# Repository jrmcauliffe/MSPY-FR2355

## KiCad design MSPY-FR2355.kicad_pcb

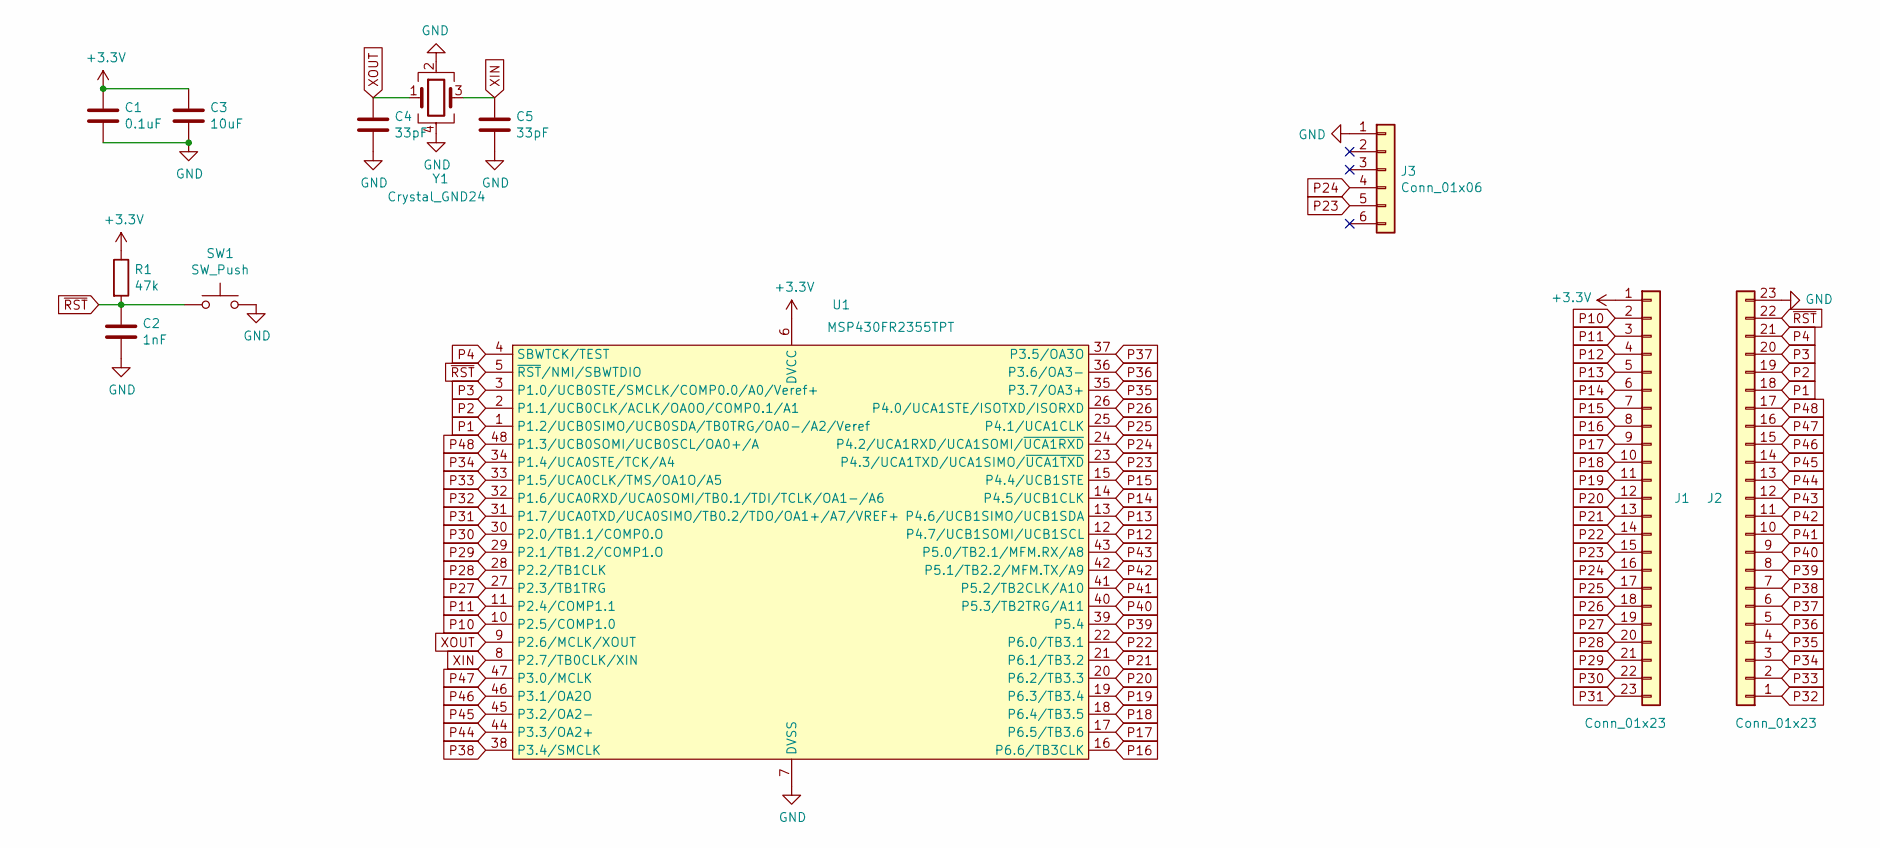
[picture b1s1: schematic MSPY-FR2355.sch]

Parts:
C1: 0.1uF; C_0603_1608Metric_Pad1.05x0.95mm_HandSolder
C2: 1nF; C_0603_1608Metric_Pad1.05x0.95mm_HandSolder
C3: 10uF; C_0603_1608Metric_Pad1.05x0.95mm_HandSolder
C4, C5: 33pF; C_0603_1608Metric_Pad1.05x0.95mm_HandSolder
J1, J2: Conn_01x23; PinHeader_1x23_P2.54mm_Vertical
J3: Conn_01x06; PinHeader_1x06_P2.54mm_Horizontal
R1: 47k; R_0603_1608Metric_Pad1.05x0.95mm_HandSolder
SW1: SW_Push; SW_PUSH_6mm_H5mm
U1: MSP430FR2355TPT; LQFP-48_7x7mm_P0.5mm
Y1: Crystal_GND24; Crystal_SMD_5032-4Pin_5.0x3.2mm

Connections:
+3V3: C1.1, C3.1, J1.1, R1.1, U1.6 (DVCC)
GND: C1.2, C2.2, C3.2, C4.2, C5.2, J2.23, J3.1, SW1.2, U1.7 (DVSS), Y1.2, Y1.4
P1: J2.18, U1.1 (P1.2/UCB0SIMO/UCB0SDA/TB0TRG/OA0-/A2/Ve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)
P2: J2.19, U1.2 (P1.1/UCB0CLK/ACLK/OA0O/COMP0.1/A1)
P3: J2.20, U1.3 (P1.0/UCB0STE/SMCLK/COMP0.0/A0/Veref+)
P4: J2.21, U1.4 (SBWTCK/TEST)
P10: J1.2, U1.10 (P2.5/COMP1.0)
P11: J1.3, U1.11 (P2.4/COMP1.1)
P12: J1.4, U1.12 (P4.7/UCB1SOMI/UCB1SCL)
P13: J1.5, U1.13 (P4.6/UCB1SIMO/UCB1SDA)
P14: J1.6, U1.14 (P4.5/UCB1CLK)
P15: J1.7, U1.15 (P4.4/UCB1STE)
P16: J1.8, U1.16 (P6.6/TB3CLK)
P17: J1.9, U1.17 (P6.5/TB3.6)
P18: J1.10, U1.18 (P6.4/TB3.5)
P19: J1.11, U1.19 (P6.3/TB3.4)
P20: J1.12, U1.20 (P6.2/TB3.3)
P21: J1.13, U1.21 (P6.1/TB3.2)
P22: J1.14, U1.22 (P6.0/TB3.1)
P23: J1.15, J3.5, U1.23 (P4.3/UCA1TXD/UCA1SIMO/~UCA1TXD~)
P24: J1.16, J3.4, U1.24 (P4.2/UCA1RXD/UCA1SOMI/~UCA1RXD~)
P25: J1.17, U1.25 (P4.1/UCA1CLK)
P26: J1.18, U1.26 (P4.0/UCA1STE/ISOTXD/ISORXD)
P27: J1.19, U1.27 (P2.3/TB1TRG)
P28: J1.20, U1.28 (P2.2/TB1CLK)
P29: J1.21, U1.29 (P2.1/TB1.2/COMP1.O)
P30: J1.22, U1.30 (P2.0/TB1.1/COMP0.O)
P31: J1.23, U1.31 (P1.7/UCA0TXD/UCA0SIMO/TB0.2/TDO/OA1+/A7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)
P32: J2.1, U1.32 (P1.6/UCA0RXD/UCA0SOMI/TB0.1/TDI/TCLK/OA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)
P33: J2.2, U1.33 (P1.5/UCA0CLK/TMS/OA1O/A5)
P34: J2.3, U1.34 (P1.4/UCA0STE/TCK/A4)
P35: J2.4, U1.35 (P3.7/OA3+)
P36: J2.5, U1.36 (P3.6/OA3-)
P37: J2.6, U1.37 (P3.5/OA3O)
P38: J2.7, U1.38 (P3.4/SMCLK)
P39: J2.8, U1.39 (P5.4)
P40: J2.9, U1.40 (P5.3/TB2TRG/A11)
P41: J2.10, U1.41 (P5.2/TB2CLK/A10)
P42: J2.11, U1.42 (P5.1/TB2.2/MFM.TX/A9)
P43: J2.12, U1.43 (P5.0/TB2.1/MFM.RX/A8)
P44: J2.13, U1.44 (P3.3/OA2+)
P45: J2.14, U1.45 (P3.2/OA2-)
P46: J2.15, U1.46 (P3.1/OA2O)
P47: J2.16, U1.47 (P3.0/MCLK)
P48: J2.17, U1.48 (P1.3/UCB0SOMI/UCB0SCL/OA0+/A)
XIN: C5.1, U1.8 (P2.7/TB0CLK/XIN), Y1.3
XOUT: C4.1, U1.9 (P2.6/MCLK/XOUT), Y1.1
~RST~: C2.1, J2.22, R1.2, SW1.1, U1.5 (~RST~/NMI/SBWTDIO)

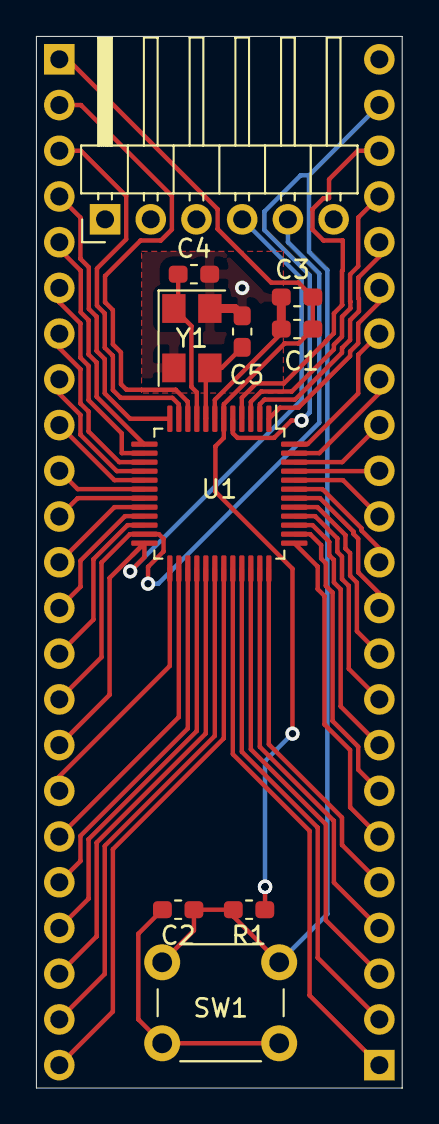
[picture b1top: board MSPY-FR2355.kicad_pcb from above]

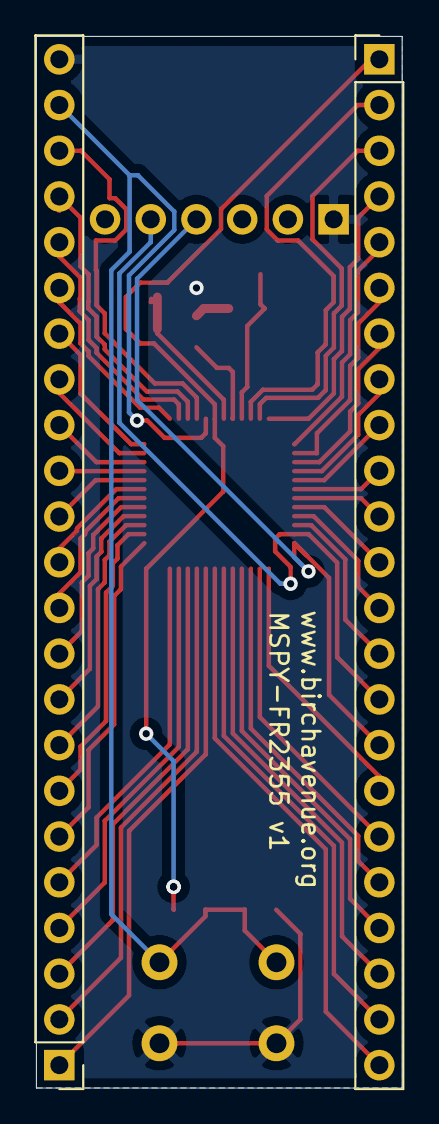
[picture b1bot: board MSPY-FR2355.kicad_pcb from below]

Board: 2 copper layers, 20.3 x 58.4 mm, 12 parts (2 on the bottom side), 48 nets.
